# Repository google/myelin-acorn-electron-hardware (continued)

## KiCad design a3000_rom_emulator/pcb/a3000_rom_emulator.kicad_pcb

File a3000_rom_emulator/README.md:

# Arcflash has moved to [github.com/myelin/arcflash](https://github.com/myelin/arcflash)

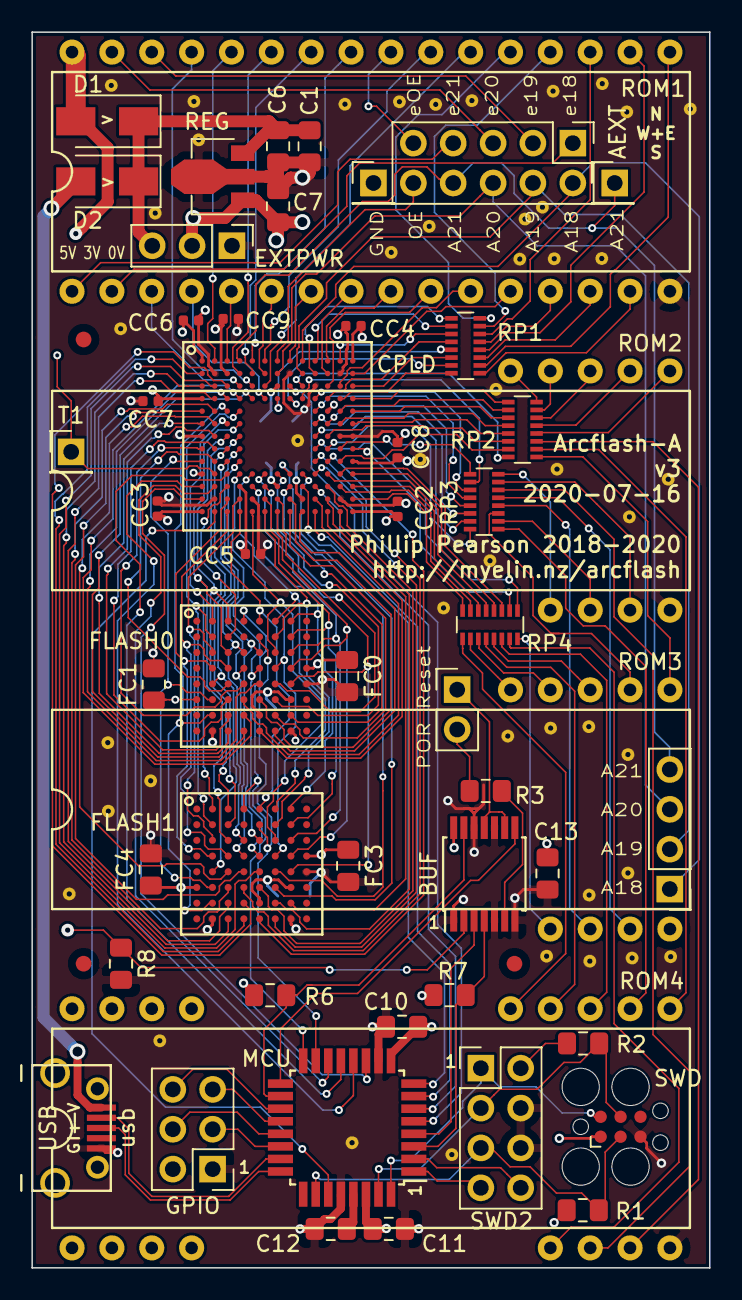
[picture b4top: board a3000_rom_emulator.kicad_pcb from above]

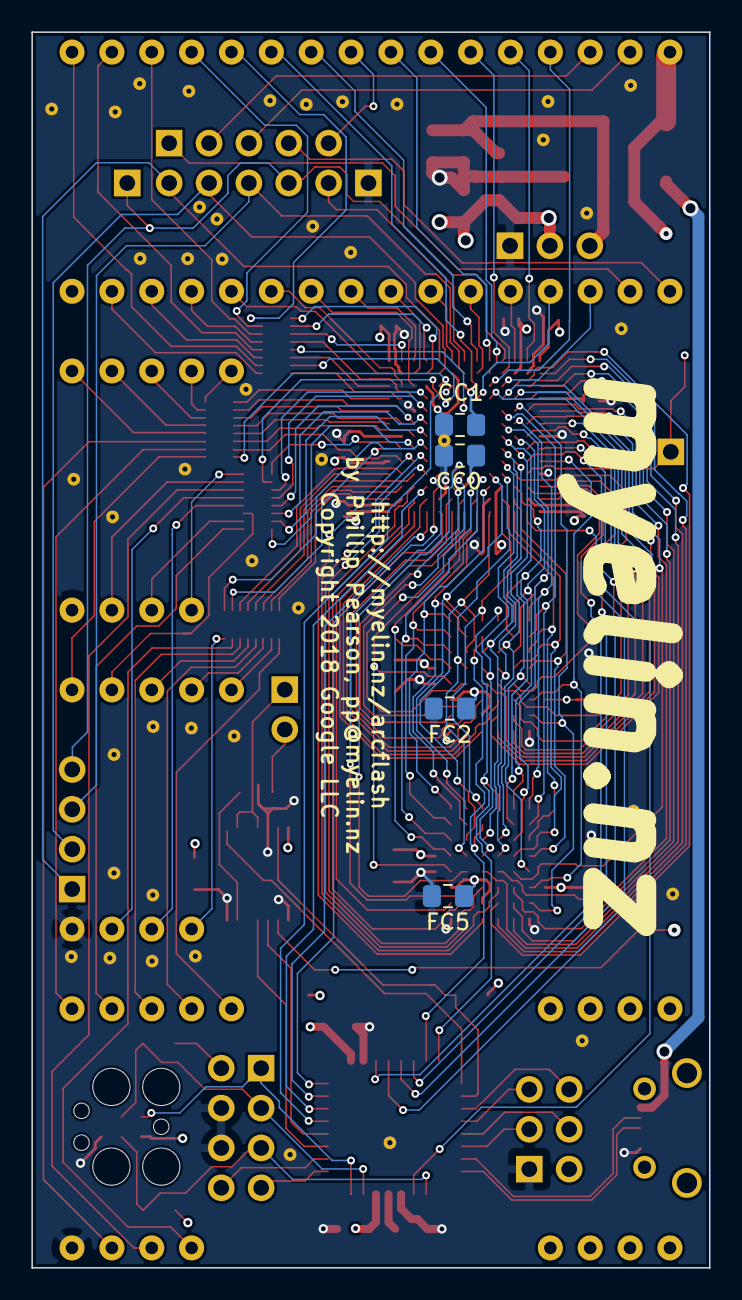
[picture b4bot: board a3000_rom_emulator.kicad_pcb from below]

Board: 4 copper layers, 43.2 x 78.7 mm, 112 parts (4 on the bottom side), 183 nets.

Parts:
A21: rom_A19; PinHeader_1x01_P2.54mm_Vertical
AEXT: Extras; PinHeader_2x05_P2.54mm_Vertical
AEXT2: Addresses; PinHeader_1x04_P2.54mm_Vertical
AEXTGND: Ground; PinHeader_1x01_P2.54mm_Vertical
BUF: 74LVC125PW; TSSOP-14_4.4x5mm_P0.65mm
C1: 10u; C_0805_2012Metric_Pad1.15x1.40mm_HandSolder
C6, C7, C12: 1u; C_0805_2012Metric_Pad1.15x1.40mm_HandSolder
C10, C11, C13: 100n; C_0805_2012Metric_Pad1.15x1.40mm_HandSolder
CC0, CC1: 100n; C_0805_2012Metric_Pad1.15x1.40mm_HandSolder
CC2, CC3, CC4, CC5, CC6, CC7, CC8, CC9: 100n; C_0402_1005Metric
CPLD: XC95144XL-10CSG144; xilinx_csg144
D1: S1ATR; D_SMA
D2: S1ATR NF; D_SMA
EXTPWR: ext pwr; PinHeader_1x03_P2.54mm_Vertical
FC0, FC1, FC2, FC3, FC4, FC5: 100n; C_0805_2012Metric_Pad1.15x1.40mm_HandSolder
FID1, FID2, FID3: FIDUCIAL; Fiducial_1mm_Dia_2mm_Outer
FLASH0, FLASH1: S29GL064S70DHI010; cypress_lae064_fbga
GPIO: gpio; PinHeader_2x03_P2.54mm_Vertical
MCU: ATSAMD21E18A-AU; TQFP-32_7x7mm_P0.8mm
R1, R6, R7, R8: 10k; R_0805_2012Metric_Pad1.15x1.40mm_HandSolder
R2: 1k; R_0805_2012Metric_Pad1.15x1.40mm_HandSolder
R3: 100R; R_0805_2012Metric_Pad1.15x1.40mm_HandSolder
REG: AP7365-33YG-XX; SOT-89-3
RESET: reset/POR; PinHeader_1x02_P2.54mm_Vertical
ROM1: ROM header; dip32_rom
ROM2, ROM3, ROM4: ROM header; dip32_rom_data_only
RP1, RP2, RP3, RP4: Pack of 8 x isolated 68R resistors; R_Array_Convex_8x0602
SWD: swd; Tag-Connect_TC2030-IDC-FP_2x03_P1.27mm_Vertical
SWD2: swd; PinHeader_2x04_P2.54mm_Vertical
T1: rom_5V; PinHeader_1x01_P2.54mm_Vertical
USB: usb; micro_usb_b_smd_molex
mech_pin1, mech_pin2, mech_pin3, mech_pin4, mech_pin5, mech_pin6, mech_pin7, mech_pin8: dip_rom_single_pin
staple_single1, staple_single2, staple_single3, staple_single4, staple_single5, staple_single6, staple_single7, staple_single8, staple_single9, staple_single10, staple_single11, staple_single12, staple_single13, staple_single14, staple_single15, staple_single16, staple_single17, staple_single18, staple_single19, staple_single20, staple_single21, staple_single22, staple_single23, staple_single24, staple_single25, staple_single26, staple_single27, staple_single28, staple_single29, staple_single30, staple_single31, staple_single32, staple_single33, staple_single34, staple_single35, staple_single36, staple_single37, staple_single38, staple_single39, staple_single40, staple_single41, staple_single42, staple_single43, staple_single44, staple_single45: via_single

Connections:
3V3: BUF.14, C7.1, C10.2, C11.2, C13.2, CC0.1, CC1.1, CC2.1, CC3.1, CC4.1, CC5.1, CC6.1, CC7.1, CC8.1, CC9.1, CPLD.A1, CPLD.A13, CPLD.B3, CPLD.C7, CPLD.D1, CPLD.J13, CPLD.L4, CPLD.L7, CPLD.N1, CPLD.N13, EXTPWR.2, FC0.1, FC1.1, FC2.1, FC3.1, FC4.1, FC5.1, FLASH0.D8, FLASH0.F1, FLASH0.F7, FLASH0.G5, FLASH1.D8, FLASH1.F1, FLASH1.F7, FLASH1.G5, GPIO.2, MCU.9, MCU.30, R1.2, R2.2, R6.2, R7.2, REG.1, SWD.1, SWD2.2
5V: C1.2, C6.2, D1.1, D2.1, EXTPWR.3, REG.3
GND: AEXTGND.1, BUF.1, BUF.5, BUF.7, BUF.10, BUF.12, C1.1, C6.1, C7.2, C10.1, C11.1, C12.1, C13.1, CC0.2, CC1.2, CC2.2, CC3.2, CC4.2, CC5.2, CC6.2, CC7.2, CC8.2, CC9.2, CPLD.B2, CPLD.B8, CPLD.B12, CPLD.C10, CPLD.E11, CPLD.G1, CPLD.G12, CPLD.G13, CPLD.K1, CPLD.M2, CPLD.M5, CPLD.M9, CPLD.M12, EXTPWR.1, FC0.2, FC1.2, FC2.2, FC3.2, FC4.2, FC5.2, FLASH0.E8, FLASH0.H2, FLASH0.H7, FLASH1.E8, FLASH1.H2, FLASH1.H7, GPIO.1, MCU.10, MCU.28, R8.2, REG.2, ROM1.16, ROM2.16, ROM3.16, ROM4.16, SWD.5, SWD2.4, SWD2.6, USB.5, staple_single1.1, staple_single2.1, staple_single3.1, staple_single4.1, staple_single5.1, staple_single6.1, staple_single7.1, staple_single8.1, staple_single9.1, staple_single10.1, staple_single11.1, staple_single12.1, staple_single13.1, staple_single14.1, staple_single15.1, staple_single16.1, staple_single17.1, staple_single18.1, staple_single19.1, staple_single20.1, staple_single21.1, staple_single22.1, staple_single23.1, staple_single24.1, staple_single25.1, staple_single26.1, staple_single27.1, staple_single28.1, staple_single29.1, staple_single30.1, staple_single31.1, staple_single32.1, staple_single33.1, staple_single34.1, staple_single35.1, staple_single36.1, staple_single37.1, staple_single38.1, staple_single39.1, staple_single40.1, staple_single41.1, staple_single42.1, staple_single43.1, staple_single44.1, staple_single45.1
USBDM: MCU.23, USB.2
USBDP: MCU.24, USB.3
VDDCORE: C12.2, MCU.29
VUSB: D2.2, USB.1
arc_POR: R3.2, RESET.2
arc_POR_R: BUF.6, R3.1
arc_RESET: BUF.9, BUF.11, RESET.1
arc_RESET_buffered: BUF.8, MCU.17
cpld_MISO: CPLD.L2, MCU.14
cpld_MOSI: CPLD.M1, MCU.11
cpld_SCK: CPLD.L1, MCU.12
cpld_SS: CPLD.K3, MCU.13
cpld_TCK: CPLD.L10, MCU.6
cpld_TDI: CPLD.L9, MCU.8
cpld_TDO: CPLD.C8, MCU.5
cpld_TMS: CPLD.N10, MCU.7
cpld_clock_from_mcu: CPLD.N2, MCU.27
flash0_DQ0: CPLD.J2, FLASH0.E3
flash0_DQ1: CPLD.F1, FLASH0.H3
flash0_DQ2: CPLD.H1, FLASH0.E4
flash0_DQ3: CPLD.D3, FLASH0.H4
flash0_DQ4: CPLD.N11, FLASH0.H5
flash0_DQ5: CPLD.D5, FLASH0.E5
flash0_DQ6: CPLD.N9, FLASH0.H6
flash0_DQ7: CPLD.L6, FLASH0.E6
flash0_DQ8: CPLD.H2, FLASH0.F3
flash0_DQ9: CPLD.G2, FLASH0.G3
flash0_DQ10: CPLD.M10, FLASH0.F4
flash0_DQ11: CPLD.D4, FLASH0.G4
flash0_DQ12: CPLD.M8, FLASH0.F5
flash0_DQ13: CPLD.N8, FLASH0.G6
flash0_DQ14: CPLD.K7, FLASH0.F6
flash0_DQ15: CPLD.L8, FLASH0.G7
flash1_DQ0: CPLD.F2, FLASH1.E3
flash1_DQ1: CPLD.C1, FLASH1.H3
flash1_DQ2: CPLD.E1, FLASH1.E4
flash1_DQ3: CPLD.B1, FLASH1.H4
flash1_DQ4: CPLD.J11, FLASH1.H5
flash1_DQ5: CPLD.C2, FLASH1.E5
flash1_DQ6: CPLD.K10, FLASH1.H6
flash1_DQ7: CPLD.K8, FLASH1.E6
flash1_DQ8: CPLD.E2, FLASH1.F3
flash1_DQ9: CPLD.D2, FLASH1.G3
flash1_DQ10: CPLD.J10, FLASH1.F4
flash1_DQ11: CPLD.C3, FLASH1.G4
flash1_DQ12: CPLD.L11, FLASH1.F5
flash1_DQ13: CPLD.N12, FLASH1.G6
flash1_DQ14: CPLD.K9, FLASH1.F6
flash1_DQ15: CPLD.M11, FLASH1.G7
flash_A0: CPLD.G4, FLASH0.E2, FLASH1.E2
flash_A1: CPLD.M3, FLASH0.D2, FLASH1.D2
flash_A2: CPLD.M4, FLASH0.C2, FLASH1.C2
flash_A3: CPLD.F3, FLASH0.A2, FLASH1.A2
flash_A4: CPLD.E4, FLASH0.B2, FLASH1.B2
flash_A5: CPLD.N3, FLASH0.D3, FLASH1.D3
flash_A6: CPLD.F4, FLASH0.C3, FLASH1.C3
flash_A7: CPLD.G3, FLASH0.A3, FLASH1.A3
flash_A8: CPLD.N6, FLASH0.B6, FLASH1.B6
flash_A9: CPLD.K5, FLASH0.A6, FLASH1.A6
flash_A10: CPLD.N5, FLASH0.C6, FLASH1.C6
flash_A11: CPLD.K4, FLASH0.D6, FLASH1.D6
flash_A12: CPLD.M6, FLASH0.B7, FLASH1.B7
flash_A13: CPLD.L5, FLASH0.A7, FLASH1.A7
flash_A14: CPLD.K6, FLASH0.C7, FLASH1.C7
flash_A15: CPLD.N7, FLASH0.D7, FLASH1.D7
flash_A16: CPLD.M7, FLASH0.E7, FLASH1.E7
flash_A17: CPLD.L3, FLASH0.B3, FLASH1.B3
flash_A18: CPLD.H3, FLASH0.C4, FLASH1.C4
flash_A19: CPLD.J4, FLASH0.D5, FLASH1.D5
flash_A20: CPLD.J3, FLASH0.D4, FLASH1.D4
flash_A21: CPLD.H4, FLASH0.C5, FLASH1.C5
flash_READY: FLASH0.A4, FLASH1.A4, MCU.16
flash_nCE: CPLD.J1, FLASH0.F2, FLASH1.F2
flash_nOE: CPLD.E3, FLASH0.G2, FLASH1.G2
flash_nRESET: FLASH0.B5, FLASH1.B5, MCU.15
flash_nWE: CPLD.N4, FLASH0.A5, FLASH1.A5
mcu_GPIO0: GPIO.3, MCU.22
mcu_GPIO1: GPIO.4, MCU.21
mcu_GPIO2: GPIO.5, MCU.20
mcu_GPIO3: GPIO.6, MCU.19
mcu_RESET: MCU.26, R1.1, SWD.3, SWD2.5
mcu_SWCLK: MCU.31, R2.1, SWD.4, SWD2.3
mcu_SWDIO: MCU.32, SWD.2, SWD2.1
mcu_debug_RXD: MCU.2, SWD2.8
mcu_debug_TXD: MCU.1, SWD2.7
ndrive_arc_POR: BUF.4, MCU.3, R7.1
ndrive_arc_RESET: BUF.13, MCU.18, R6.1
rom_5V: BUF.2, CPLD.K2, D1.2, R8.1, ROM1.32, T1.1
rom_5V_buffered: BUF.3, MCU.4
rom_A0: CPLD.B13, ROM1.12
rom_A1: CPLD.C12, ROM1.11
rom_A2: CPLD.C11, ROM1.10
rom_A3: CPLD.A11, ROM1.9
rom_A4: CPLD.B11, ROM1.8
rom_A5: CPLD.A8, ROM1.7
rom_A6: CPLD.B6, ROM1.6
rom_A7: CPLD.A3, ROM1.5
rom_A8: CPLD.B4, ROM1.27
rom_A9: CPLD.B5, ROM1.26
rom_A10: CPLD.A6, ROM1.23
rom_A11: CPLD.A5, ROM1.25
rom_A12: CPLD.D6, ROM1.4
rom_A13: CPLD.A2, ROM1.28
rom_A14: CPLD.C5, ROM1.29
rom_A15: CPLD.C4, ROM1.3
rom_A16: AEXT.2, AEXT2.1, CPLD.A9
rom_A16_ext: AEXT.1, ROM1.2
rom_A17: AEXT.4, AEXT2.2, CPLD.B9
rom_A17_ext: AEXT.3, ROM1.30
rom_A18: AEXT.6, AEXT2.3, CPLD.B7
rom_A18_ext: AEXT.5, ROM1.31
rom_A19: A21.1, AEXT.8, AEXT2.4, CPLD.A4
rom_A19_ext: AEXT.7, ROM1.1
rom_D0: CPLD.D11, RP1.4
rom_D0_ext: ROM1.13, RP1.13
rom_D1: CPLD.C13, RP1.6
rom_D1_ext: ROM1.14, RP1.11
rom_D2: CPLD.D12, RP1.8
rom_D2_ext: ROM1.15, RP1.9
rom_D3: CPLD.D8, RP1.7
rom_D3_ext: ROM1.17, RP1.10
rom_D4: CPLD.D7, RP1.5
rom_D4_ext: ROM1.18, RP1.12
rom_D5: CPLD.A12, RP1.3
rom_D5_ext: ROM1.19, RP1.14
rom_D6: CPLD.A10, RP1.2
rom_D6_ext: ROM1.20, RP1.15
rom_D7: CPLD.B10, RP1.1
rom_D7_ext: ROM1.21, RP1.16
rom_D8: CPLD.H12, RP3.1
rom_D8_ext: ROM2.13, RP3.16
rom_D9: CPLD.G10, RP3.7
rom_D9_ext: ROM2.14, RP3.10
rom_D10: CPLD.D9, RP3.2
rom_D10_ext: ROM2.15, RP3.15
rom_D11: CPLD.F13, RP2.5
rom_D11_ext: ROM2.17, RP2.12
rom_D12: CPLD.F12, RP2.4
rom_D12_ext: ROM2.18, RP2.13
rom_D13: CPLD.E13, RP2.3
rom_D13_ext: ROM2.19, RP2.14
rom_D14: CPLD.E12, RP2.2
rom_D14_ext: ROM2.20, RP2.15
rom_D15: CPLD.D13, RP2.1
rom_D15_ext: ROM2.21, RP2.16
rom_D16: CPLD.H10, RP4.1
rom_D16_ext: ROM3.13, RP4.16
rom_D17: CPLD.F11, RP3.5
rom_D17_ext: ROM3.14, RP3.12
rom_D18: CPLD.E10, RP3.4
rom_D18_ext: ROM3.15, RP3.13
rom_D19: CPLD.C9, RP2.8
rom_D19_ext: ROM3.17, RP2.9
rom_D20: CPLD.F10, RP3.6
rom_D20_ext: ROM3.18, RP3.11
rom_D21: CPLD.K13, RP4.4
rom_D21_ext: ROM3.19, RP4.13
rom_D22: CPLD.L13, RP4.6
rom_D22_ext: ROM3.20, RP4.11
rom_D23: CPLD.L12, RP4.7
rom_D23_ext: ROM3.21, RP4.10
rom_D24: CPLD.H13, RP4.2
rom_D24_ext: ROM4.13, RP4.15
rom_D25: CPLD.D10, RP3.3
rom_D25_ext: ROM4.14, RP3.14
rom_D26: CPLD.G11, RP2.6
rom_D26_ext: ROM4.15, RP2.11
rom_D27: CPLD.J12, RP2.7
rom_D27_ext: ROM4.17, RP2.10
rom_D28: CPLD.H11, RP3.8
rom_D28_ext: ROM4.18, RP3.9
rom_D29: CPLD.K12, RP4.3
rom_D29_ext: ROM4.19, RP4.14
rom_D30: CPLD.K11, RP4.5
rom_D30_ext: ROM4.20, RP4.12
rom_D31: CPLD.M13, RP4.8
rom_D31_ext: ROM4.21, RP4.9
rom_nCS: CPLD.C6, ROM1.22
rom_nOE: AEXT.10, CPLD.A7
rom_nOE_ext: AEXT.9, ROM1.24

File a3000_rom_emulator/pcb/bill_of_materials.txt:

Identifier	Value	Description	KiCad package
RP1	Pack of 8 x isolated 68R resistors	8 x 68R pack; https://www.digikey.com/product-detail/en/panasonic-electron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	Resistor_SMD:R_Array_Convex_8x0602
RP2	Pack of 8 x isolated 68R resistors	8 x 68R pack; https://www.digikey.com/product-detail/en/panasonic-electron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	Resistor_SMD:R_Array_Convex_8x0602
RP3	Pack of 8 x isolated 68R resistors	8 x 68R pack; https://www.digikey.com/product-detail/en/panasonic-electron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	Resistor_SMD:R_Array_Convex_8x0602
RP4	Pack of 8 x isolated 68R resistors	8 x 68R pack; https://www.digikey.com/product-detail/en/panasonic-electron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	Resistor_SMD:R_Array_Convex_8x0602
CC2	100n	Capacitor 0402: 100n	Capacitor_SMD:C_0402_1005Metric
CC3	100n	Capacitor 0402: 100n	Capacitor_SMD:C_0402_1005Metric
CC4	100n	Capacitor 0402: 100n	Capacitor_SMD:C_0402_1005Metric
CC5	100n	Capacitor 0402: 100n	Capacitor_SMD:C_0402_1005Metric
CC6	100n	Capacitor 0402: 100n	Capacitor_SMD:C_0402_1005Metric
CC7	100n	Capacitor 0402: 100n	Capacitor_SMD:C_0402_1005Metric
CC8	100n	Capacitor 0402: 100n	Capacitor_SMD:C_0402_1005Metric
CC9	100n	Capacitor 0402: 100n	Capacitor_SMD:C_0402_1005Metric
C10	100n	Capacitor 0805: 100n	Capacitor_SMD:C_0805_2012Metric_Pad1.15x1.40mm_HandSolder
C11	100n	Capacitor 0805: 100n	Capacitor_SMD:C_0805_2012Metric_Pad1.15x1.40mm_HandSolder
C13	100n	Capacitor 0805: 100n	Capacitor_SMD:C_0805_2012Metric_Pad1.15x1.40mm_HandSolder
CC0	100n	Capacitor 0805: 100n	Capacitor_SMD:C_0805_2012Metric_Pad1.15x1.40mm_HandSolder
CC1	100n	Capacitor 0805: 100n	Capacitor_SMD:C_0805_2012Metric_Pad1.15x1.40mm_HandSolder
FC0	100n	Capacitor 0805: 100n	Capacitor_SMD:C_0805_2012Metric_Pad1.15x1.40mm_HandSolder
FC1	100n	Capacitor 0805: 100n	Capacitor_SMD:C_0805_2012Metric_Pad1.15x1.40mm_HandSolder
FC2	100n	Capacitor 0805: 100n	Capacitor_SMD:C_0805_2012Metric_Pad1.15x1.40mm_HandSolder
FC3	100n	Capacitor 0805: 100n	Capacitor_SMD:C_0805_2012Metric_Pad1.15x1.40mm_HandSolder
FC4	100n	Capacitor 0805: 100n	Capacitor_SMD:C_0805_2012Metric_Pad1.15x1.40mm_HandSolder
FC5	100n	Capacitor 0805: 100n	Capacitor_SMD:C_0805_2012Metric_Pad1.15x1.40mm_HandSolder
C1	10u	Capacitor 0805: 10u	Capacitor_SMD:C_0805_2012Metric_Pad1.15x1.40mm_HandSolder
C12	1u	Capacitor 0805: 1u	Capacitor_SMD:C_0805_2012Metric_Pad1.15x1.40mm_HandSolder
C6	1u	Capacitor 0805: 1u	Capacitor_SMD:C_0805_2012Metric_Pad1.15x1.40mm_HandSolder
C7	1u	Capacitor 0805: 1u	Capacitor_SMD:C_0805_2012Metric_Pad1.15x1.40mm_HandSolder
D1	S1ATR	Diode Rectifier; https://www.digikey.com/products/en?keywords=1655-1502-1-ND	Diode_SMD:D_SMA
D2	S1ATR NF	Diode Rectifier; https://www.digikey.com/products/en?keywords=1655-1502-1-ND	Diode_SMD:D_SMA
MCU	ATSAMD21E18A-AU	IC ARM MCU; https://www.digikey.com/products/en?keywords=ATSAMD21E18A-AU-ND	Package_QFP:TQFP-32_7x7mm_P0.8mm
CPLD	XC95144XL-10CSG144	IC CPLD Xilinx 144MC	myelin-kicad:xilinx_csg144
REG	AP7365-33YG-XX	IC LDO 3.3V regulator; https://www.digikey.com/products/en?keywords=AP7365-33YG-13DICT-ND	Package_TO_SOT_SMD:SOT-89-3
BUF	74LVC125PW	IC buffer 4-bit OC LVT; https://www.digikey.com/product-detail/en/74LVT125PW%2c118/1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	Package_SO:TSSOP-14_4.4x5mm_P0.65mm
FLASH0	S29GL064S70DHI010	IC flash 64Mbit; https://www.digikey.com/products/en?keywords=2015-S29GL064S7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	myelin-kicad:cypress_lae064_fbga
FLASH1	S29GL064S70DHI010	IC flash 64Mbit; https://www.digikey.com/products/en?keywords=2015-S29GL064S7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	myelin-kicad:cypress_lae064_fbga
ROM1	ROM header	Pin adapter to emulate a 600mil 32-pin DIP; round pin header strip from Aliexpress	myelin-kicad:dip32_rom
ROM2	ROM header	Pin adapter to emulate a 600mil 32-pin DIP; round pin header strip from Aliexpress	myelin-kicad:dip32_rom_data_only
ROM3	ROM header	Pin adapter to emulate a 600mil 32-pin DIP; round pin header strip from Aliexpress	myelin-kicad:dip32_rom_data_only
ROM4	ROM header	Pin adapter to emulate a 600mil 32-pin DIP; round pin header strip from Aliexpress	myelin-kicad:dip32_rom_data_only
AEXT2	Addresses	Pin header	Connector_PinHeader_2.54mm:PinHeader_1x04_P2.54mm_Vertical
AEXT	Extras	Pin header	Connector_PinHeader_2.54mm:PinHeader_2x05_P2.54mm_Vertical
AEXTGND	Ground	Pin header	Connector_PinHeader_2.54mm:PinHeader_1x01_P2.54mm_Vertical
T1	rom_5V	Pin header	Connector_PinHeader_2.54mm:PinHeader_1x01_P2.54mm_Vertical
A21	rom_A19	Pin header	Connector_PinHeader_2.54mm:PinHeader_1x01_P2.54mm_Vertical
RESET	reset/POR	Pin header - 1x2 0.1 inch male	Connector_PinHeader_2.54mm:PinHeader_1x02_P2.54mm_Vertical
GPIO	gpio	Pin header NF	Connector_PinHeader_2.54mm:PinHeader_2x03_P2.54mm_Vertical
SWD2	swd	Pin header NF	Connector_PinHeader_2.54mm:PinHeader_2x04_P2.54mm_Vertical
EXTPWR	ext pwr	Pin header NF - 1x3 0.1 inch male	Connector_PinHeader_2.54mm:PinHeader_1x03_P2.54mm_Vertical
R3	100R	Resistor 0805: 100R	Resistor_SMD:R_0805_2012Metric_Pad1.15x1.40mm_HandSolder
R1	10k	Resistor 0805: 10k	Resistor_SMD:R_0805_2012Metric_Pad1.15x1.40mm_HandSolder
R6	10k	Resistor 0805: 10k	Resistor_SMD:R_0805_2012Metric_Pad1.15x1.40mm_HandSolder
R7	10k	Resistor 0805: 10k	Resistor_SMD:R_0805_2012Metric_Pad1.15x1.40mm_HandSolder
R8	10k	Resistor 0805: 10k	Resistor_SMD:R_0805_2012Metric_Pad1.15x1.40mm_HandSolder
R2	1k	Resistor 0805: 1k	Resistor_SMD:R_0805_2012Metric_Pad1.15x1.40mm_HandSolder
USB	usb	Socket Micro USB, Molex 1050170001; https://www.digikey.com/products/en?keywords=WM1399CT-ND	myelin-kicad:micro_usb_b_smd_molex

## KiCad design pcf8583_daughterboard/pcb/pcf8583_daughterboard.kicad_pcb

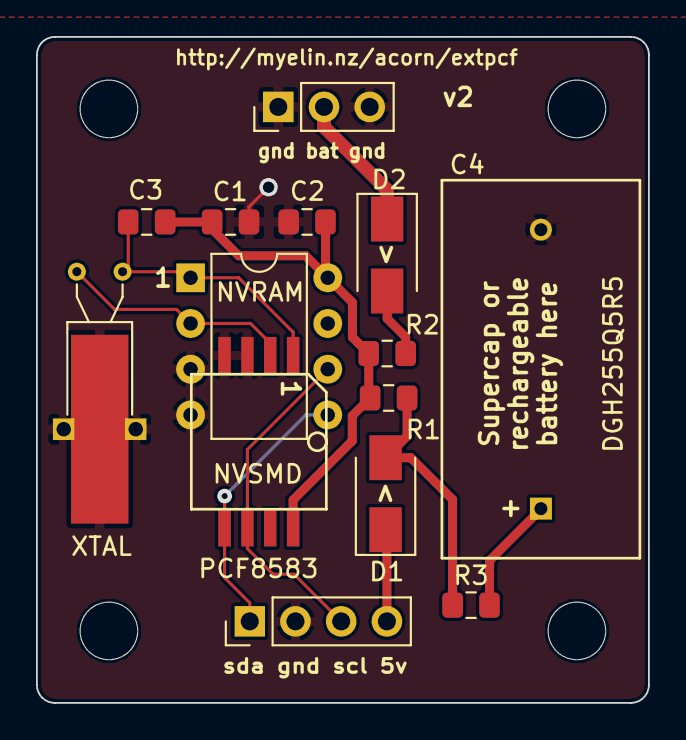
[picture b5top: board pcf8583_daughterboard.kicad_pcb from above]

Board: 2 copper layers, 34.0 x 37.0 mm, 14 parts (0 on the bottom side), 11 nets.

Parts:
BATT: Battery; PinHeader_1x03_P2.54mm_Vertical
C1: 10u; C_0805_2012Metric_Pad1.15x1.40mm_HandSolder
C2: 100n; C_0805_2012Metric_Pad1.15x1.40mm_HandSolder
C3: 15p; C_0805_2012Metric_Pad1.15x1.40mm_HandSolder
C4: DGH255Q5R5; dgh255q5r5
D1, D2: S1ATR; D_SMA
HDR: Ext; PinHeader_1x04_P2.54mm_Vertical
NVRAM: PCF8583; DIP-8_W7.62mm
NVSMD: PCF8583; so8_pcf8583t_7.5x7.5mm
R1, R2: 47R; R_0805_2012Metric_Pad1.15x1.40mm_HandSolder
R3: 180R; R_0805_2012Metric_Pad1.15x1.40mm_HandSolder
XTAL: 32.768kHz; Crystal_AT310_D3.0mm_L10.0mm_Horizontal_1EP_style2

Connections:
5V: D1.1, HDR.4
5VD_cat: D1.2, R1.1, R3.1
BATT: BATT.2, D2.1
BATTD_cat: D2.2, R2.1
GND: BATT.1, BATT.3, C1.1, C2.1, C4.2, HDR.2, NVRAM.3, NVRAM.4, NVSMD.3, NVSMD.4, XTAL.3
NVR_POWER: C1.2, C2.2, C3.2, NVRAM.8, NVSMD.8, R1.2, R2.2
OSCI: C3.1, NVRAM.1, NVSMD.1, XTAL.2
OSCO: NVRAM.2, NVSMD.2, XTAL.1
SCL: HDR.3, NVRAM.6, NVSMD.6
SDA: HDR.1, NVRAM.5, NVSMD.5
supercap_P: C4.1, R3.2

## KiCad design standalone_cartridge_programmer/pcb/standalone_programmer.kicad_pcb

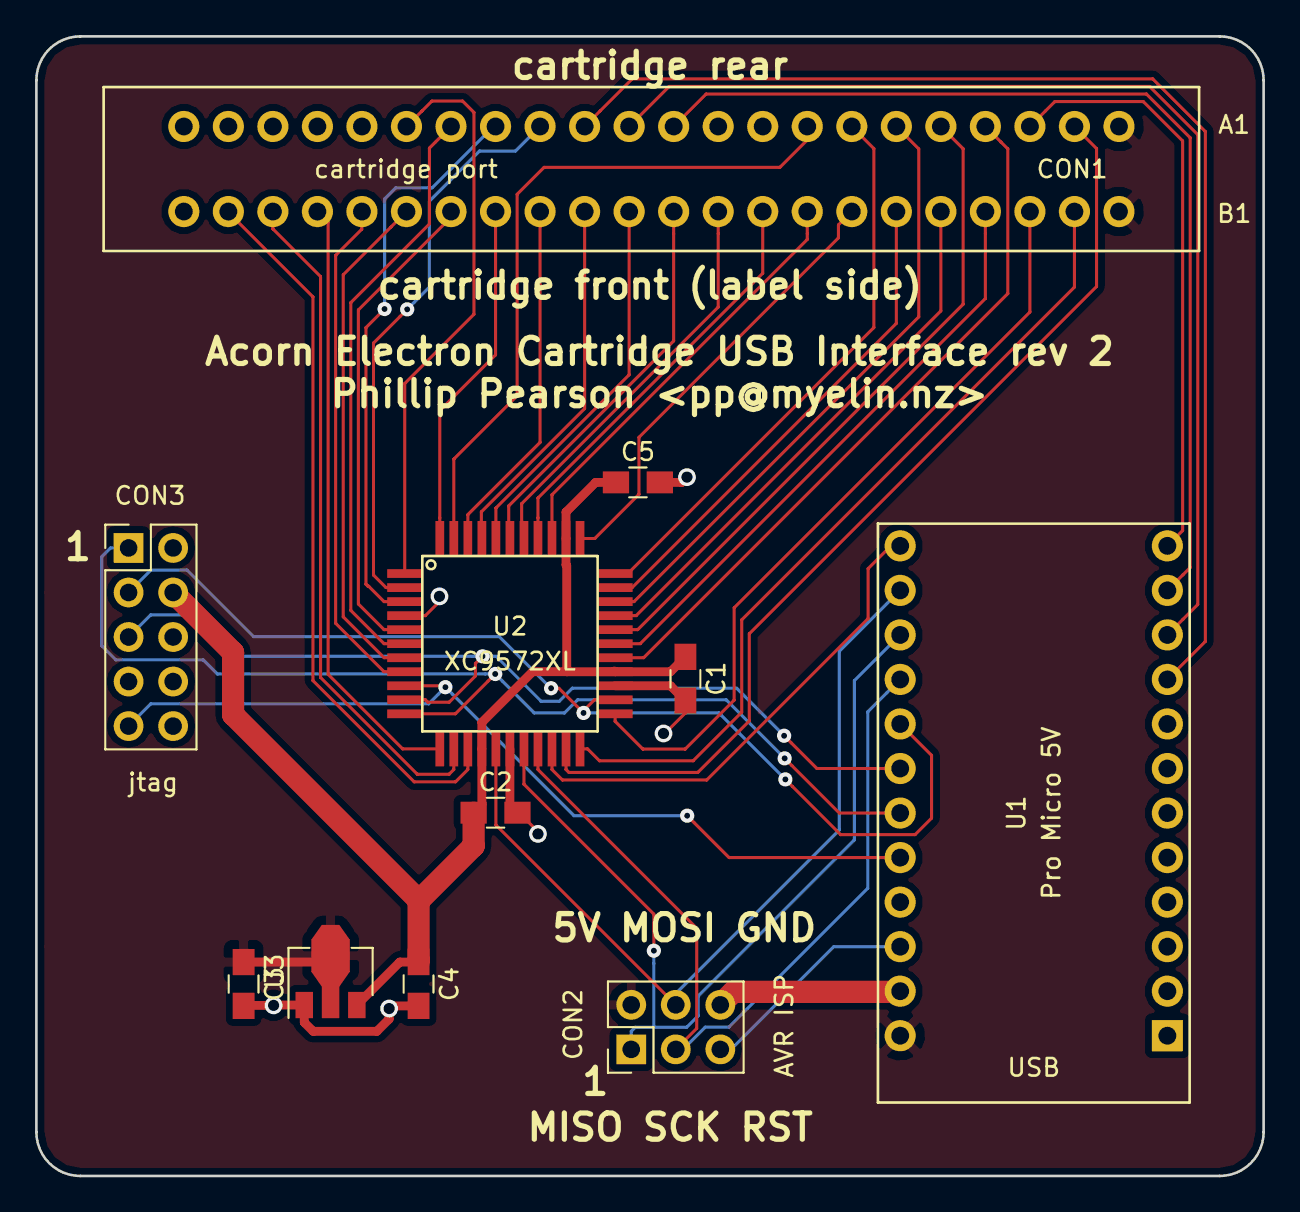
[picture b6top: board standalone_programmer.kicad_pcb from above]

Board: 2 copper layers, 70.0 x 65.0 mm, 11 parts (0 on the bottom side), 46 nets.

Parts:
C1, C2, C5: 100n; C_0805_HandSoldering
C3, C4: 1u; C_0805_HandSoldering
CON1: cartridge port; acorn_electron_cartridge_socket
CON2: AVR ISP; Pin_Header_Straight_2x03_Pitch2.54mm
CON3: jtag; Pin_Header_Straight_2x05_Pitch2.54mm
U1: Pro Micro 5V; pro_micro
U2: XC9572XL; xilinx_vqg44
U3: MCP1700T-3302E/MB; SOT-89-3

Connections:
3V3: C1.1, C2.1, C4.1, C5.1, CON3.4, U2.15, U2.26, U2.35, U3.3
5V: C3.1, CON1.A1, CON1.B1, CON2.2, U1.24, U3.2
GND: C1.2, C2.2, C3.2, C4.2, C5.2, CON1.A22, CON1.B22, CON2.6, CON3.2, CON3.10, U1.3, U1.4, U1.23, U2.4, U2.17, U2.25, U3.1
avr_MISO: CON2.1, U1.15, U2.18
avr_MOSI: CON2.4, U1.14, U2.16
avr_RST: CON2.5, U1.22
avr_SCK: CON2.3, U1.16, U2.19
cart_16MHZ: CON1.A17, U2.1
cart_A0: CON1.B18, U2.8
cart_A1: CON1.B17, U2.7
cart_A2: CON1.B16, U2.5
cart_A3: CON1.B15, U2.44
cart_A4: CON1.B14, U2.42
cart_A5: CON1.B13, U2.41
cart_A6: CON1.B12, U2.40
cart_A7: CON1.B11, U2.39
cart_A8: CON1.A5, U2.29
cart_A9: CON1.B5, U2.30
cart_A10: CON1.B2, U2.22
cart_A11: CON1.B4, U2.28
cart_A12: CON1.A7, U2.33
cart_A13: CON1.A6, U2.31
cart_D0: CON1.B19, U2.12
cart_D1: CON1.B21, U2.14
cart_D2: CON1.B20, U2.13
cart_D3: CON1.B3, U2.23
cart_D4: CON1.B9, U2.37
cart_D5: CON1.B8, U2.36
cart_D6: CON1.B7, U2.34
cart_D7: CON1.B6, U2.32
cart_PHI0: CON1.A8, U2.43
cart_ROMQA: CON1.A16, U2.6
cart_RnW: CON1.A4, U2.27
cart_nINFC: CON1.A14, U2.2
cart_nINFD: CON1.A15, U2.3
cart_nIRQ: CON1.A13, U1.9
cart_nNMI: CON1.A12, U1.10
cart_nOE: CON1.A2, U2.21
cart_nOE2: CON1.B10, U2.38
cart_nRDY: CON1.A11, U1.11
cart_nRST: CON1.A3, U1.12
cpld_SS: U1.13, U2.20
cpld_TCK: CON3.1, U1.19, U2.11
cpld_TDI: CON3.9, U1.20, U2.9
cpld_TDO: CON3.3, U1.17, U2.24
cpld_TMS: CON3.5, U1.18, U2.10

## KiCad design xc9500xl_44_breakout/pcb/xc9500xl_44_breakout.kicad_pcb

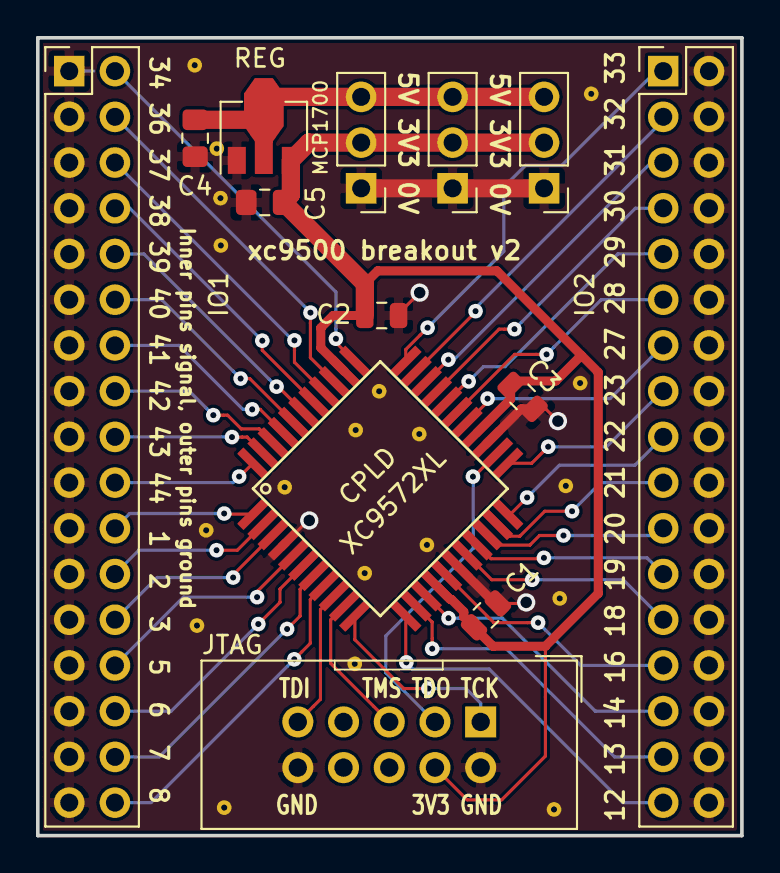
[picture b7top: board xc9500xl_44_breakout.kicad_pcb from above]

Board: 2 copper layers, 39.1 x 44.3 mm, 32 parts (0 on the bottom side), 41 nets.

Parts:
C1, C2: 100n; C_0805_2012Metric
C3: 1u; C_0805_2012Metric
C4, C5: 1u; C_0805_2012Metric_Pad1.15x1.40mm_HandSolder
CPLD: XC9572XL; xilinx_vqg44
EXTPWR1, EXTPWR2, EXTPWR3: ext pwr; PinHeader_1x03_P2.54mm_Vertical
IO1, IO2: CPLD IO; PinHeader_2x17_P2.54mm_Vertical
JTAG: jtag; IDC-Header_2x05_P2.54mm_Vertical
REG: MCP1700T-3302E/MB; SOT-89-3
staple_single1, staple_single2, staple_single3, staple_single4, staple_single5, staple_single6, staple_single7, staple_single8, staple_single9, staple_single10, staple_single11, staple_single12, staple_single13, staple_single14, staple_single15, staple_single16, staple_single17, staple_single18, staple_single19: via_single

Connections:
3V3: C1.1, C2.1, C3.1, C5.1, CPLD.15, CPLD.26, CPLD.35, EXTPWR1.2, EXTPWR2.2, EXTPWR3.2, JTAG.4, REG.3
5V: C4.2, EXTPWR1.3, EXTPWR2.3, EXTPWR3.3, REG.2
GND: C1.2, C2.2, C3.2, C4.1, C5.2, CPLD.4, CPLD.17, CPLD.25, EXTPWR1.1, EXTPWR2.1, EXTPWR3.1, IO1.1, IO1.3, IO1.5, IO1.7, IO1.9, IO1.11, IO1.13, IO1.15, IO1.17, IO1.19, IO1.21, IO1.23, IO1.25, IO1.27, IO1.29, IO1.31, IO1.33, IO2.2, IO2.4, IO2.6, IO2.8, IO2.10, IO2.12, IO2.14, IO2.16, IO2.18, IO2.20, IO2.22, IO2.24, IO2.26, IO2.28, IO2.30, IO2.32, IO2.34, JTAG.2, JTAG.10, REG.1, staple_single1.1, staple_single2.1, staple_single3.1, staple_single4.1, staple_single5.1, staple_single6.1, staple_single7.1, staple_single8.1, staple_single9.1, staple_single10.1, staple_single11.1, staple_single12.1, staple_single13.1, staple_single14.1, staple_single15.1, staple_single16.1, staple_single17.1, staple_single18.1, staple_single19.1
TCK: CPLD.11, JTAG.1
TDI: CPLD.9, JTAG.9
TDO: CPLD.24, JTAG.3
TMS: CPLD.10, JTAG.5
pin1_gck3: CPLD.1, IO1.22
pin2: CPLD.2, IO1.24
pin3: CPLD.3, IO1.26
pin5: CPLD.5, IO1.28
pin6: CPLD.6, IO1.30
pin7: CPLD.7, IO1.32
pin8: CPLD.8, IO1.34
pin12: CPLD.12, IO2.33
pin13: CPLD.13, IO2.31
pin14: CPLD.14, IO2.29
pin16: CPLD.16, IO2.27
pin18: CPLD.18, IO2.25
pin19: CPLD.19, IO2.23
pin20: CPLD.20, IO2.21
pin21: CPLD.21, IO2.19
pin22: CPLD.22, IO2.17
pin23: CPLD.23, IO2.15
pin27: CPLD.27, IO2.13
pin28: CPLD.28, IO2.11
pin29: CPLD.29, IO2.9
pin30: CPLD.30, IO2.7
pin31: CPLD.31, IO2.5
pin32: CPLD.32, IO2.3
pin33_GSR: CPLD.33, IO2.1
pin34_GTS2: CPLD.34, IO1.2
pin36_GTS1: CPLD.36, IO1.4
pin37: CPLD.37, IO1.6
pin38: CPLD.38, IO1.8
pin39: CPLD.39, IO1.10
pin40: CPLD.40, IO1.12
pin41: CPLD.41, IO1.14
pin42: CPLD.42, IO1.16
pin43_gck1: CPLD.43, IO1.18
pin44_gck2: CPLD.44, IO1.20

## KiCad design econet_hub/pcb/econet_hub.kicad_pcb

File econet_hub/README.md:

Econet hub
==========

http://myelin.nz/acorn/ecohub

A simple board that provides an Econet clock and biasing, and a bunch
of Econet sockets.

Status and history
------------------

I haven't tested this, but [https://stardot.org.uk/forums/viewtopic.php?f=3&t=15049](lcww1 on Stardot has), and it looks like they work well.

Revision 1 had a bug with the ATTINY85 footprint; it was too narrow,
so to solder the chip on, I had to turn it into a J-lead package by
bending its legs underneath.

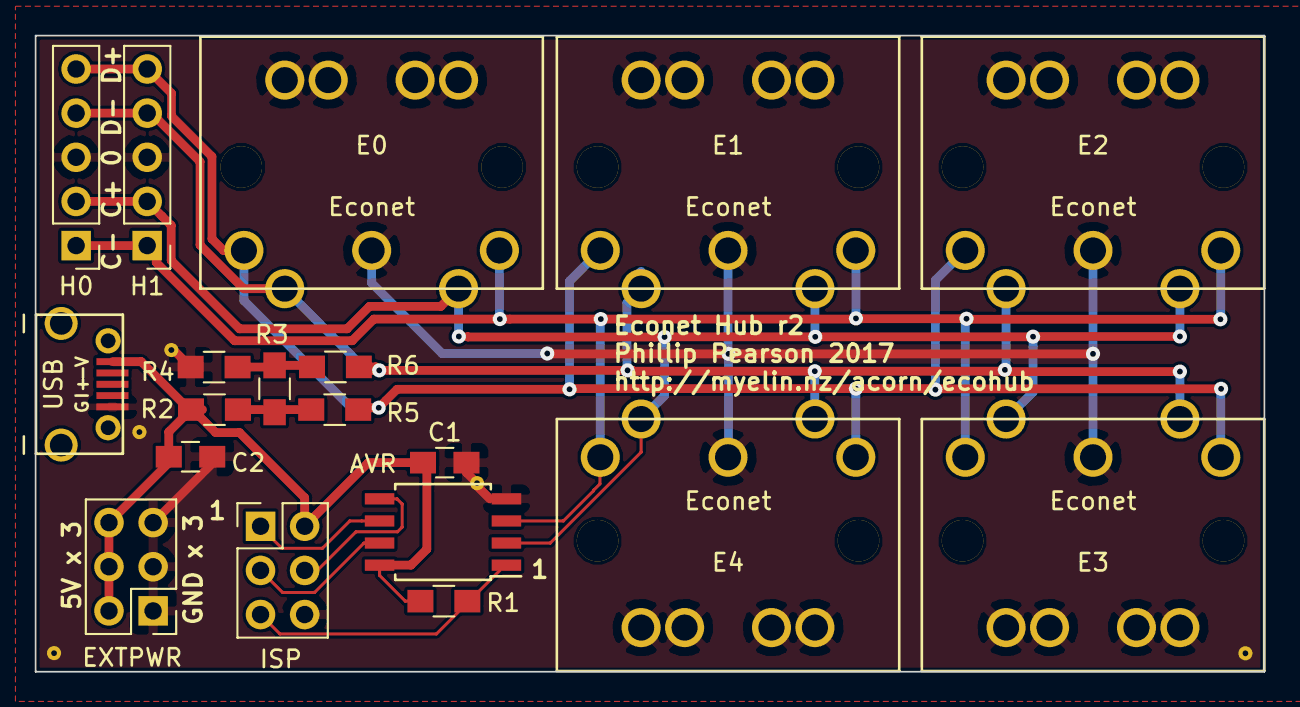
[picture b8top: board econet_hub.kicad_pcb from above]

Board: 2 copper layers, 70.7 x 36.6 mm, 24 parts (0 on the bottom side), 12 nets.

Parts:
AVR: ATTINY85-20SU; SOIJ-8_5.3x5.3mm_Pitch1.27mm
C1: 100n; C_0805_HandSoldering
C2: 10u; C_0805_HandSoldering
E0, E1, E2, E3, E4: Econet; din_5_econet_pcb_mount
EXTPWR: ext pwr; Pin_Header_Straight_2x03_Pitch2.54mm
H0, H1: Econet; Pin_Header_Straight_1x05_Pitch2.54mm
ISP: avr isp; Pin_Header_Straight_2x03_Pitch2.54mm
R1: 10k; R_0805_HandSoldering
R2, R4: 1k; R_0805_HandSoldering
R3: 220R; R_0805_HandSoldering
R5, R6: 56R; R_0805_HandSoldering
USB: usb; micro_usb_b_smd_molex
staple_single1, staple_single2, staple_single3, staple_single4, staple_single5: via_single

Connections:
5V: AVR.8, C1.1, C2.1, EXTPWR.2, EXTPWR.4, EXTPWR.6, ISP.2, R1.1, R2.1, USB.1
GND: AVR.4, C1.2, C2.2, E0.2, E0.S1, E0.S2, E0.S3, E0.S4, E1.2, E1.S1, E1.S2, E1.S3, E1.S4, E2.2, E2.S1, E2.S2, E2.S3, E2.S4, E3.2, E3.S1, E3.S2, E3.S3, E3.S4, E4.2, E4.S1, E4.S2, E4.S3, E4.S4, EXTPWR.1, EXTPWR.3, EXTPWR.5, H0.3, H1.3, ISP.6, R4.2, USB.5, staple_single1.1, staple_single2.1, staple_single3.1, staple_single4.1, staple_single5.1
avr_MISO: AVR.6, ISP.1
avr_MOSI: AVR.5, ISP.4
avr_SCK: AVR.7, ISP.3
avr_nRESET: AVR.1, ISP.5, R1.2
bias_M: R3.2, R4.1, R6.1
bias_P: R2.2, R3.1, R5.1
econet_clock_line_M: AVR.3, E0.3, E1.3, E2.3, E3.3, E4.3, H0.1, H1.1
econet_clock_line_P: AVR.2, E0.5, E1.5, E2.5, E3.5, E4.5, H0.2, H1.2
econet_data_line_M: E0.4, E1.4, E2.4, E3.4, E4.4, H0.4, H1.4, R6.2
econet_data_line_P: E0.1, E1.1, E2.1, E3.1, E4.1, H0.5, H1.5, R5.2

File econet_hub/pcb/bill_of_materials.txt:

Identifier	Value	Description	KiCad package
AVR	ATTINY85-20SU	ATTINY85 in 8S2 package (0.208 inch / 5.3 mm wide SOIC-8)	Housings_SOIC:SOIJ-8_5.3x5.3mm_Pitch1.27mm
C1	100n	100n capacitor in 0805 package	Capacitors_SMD:C_0805_HandSoldering
C2	10u	10u capacitor in 0805 package	Capacitors_SMD:C_0805_HandSoldering
E0	Econet	5-pin DIN socket, as for a MIDI cable, with zig-zag pin layout.  Compare pinout against PCB because several variants exist.	myelin-kicad:din_5_econet_pcb_mount
E1	Econet	5-pin DIN socket, as for a MIDI cable, with zig-zag pin layout.  Compare pinout against PCB because several variants exist.	myelin-kicad:din_5_econet_pcb_mount
E2	Econet	5-pin DIN socket, as for a MIDI cable, with zig-zag pin layout.  Compare pinout against PCB because several variants exist.	myelin-kicad:din_5_econet_pcb_mount
E3	Econet	5-pin DIN socket, as for a MIDI cable, with zig-zag pin layout.  Compare pinout against PCB because several variants exist.	myelin-kicad:din_5_econet_pcb_mount
E4	Econet	5-pin DIN socket, as for a MIDI cable, with zig-zag pin layout.  Compare pinout against PCB because several variants exist.	myelin-kicad:din_5_econet_pcb_mount
EXTPWR	ext pwr	1x3 0.1 inch male header	Pin_Headers:Pin_Header_Straight_2x03_Pitch2.54mm
H0	Econet	1x5 0.1 inch male header	Pin_Headers:Pin_Header_Straight_1x05_Pitch2.54mm
H1	Econet	1x5 0.1 inch male header	Pin_Headers:Pin_Header_Straight_1x05_Pitch2.54mm
ISP	avr isp	2x3 0.1 inch header for AVR programming (OPTIONAL)	Pin_Headers:Pin_Header_Straight_2x03_Pitch2.54mm
R1	10k	10k resistor in 0805 package	Resistors_SMD:R_0805_HandSoldering
R2	1k	1k resistor in 0805 package	Resistors_SMD:R_0805_HandSoldering
R3	220R	220R resistor in 0805 package	Resistors_SMD:R_0805_HandSoldering
R4	1k	1k resistor in 0805 package	Resistors_SMD:R_0805_HandSoldering
R5	56R	56R resistor in 0805 package	Resistors_SMD:R_0805_HandSoldering
R6	56R	56R resistor in 0805 package	Resistors_SMD:R_0805_HandSoldering
USB	usb	Molex 1050170001 (Digikey WM1399CT-ND) surface mount micro USB socket with mounting holes.	myelin-kicad:micro_usb_b_smd_molex
